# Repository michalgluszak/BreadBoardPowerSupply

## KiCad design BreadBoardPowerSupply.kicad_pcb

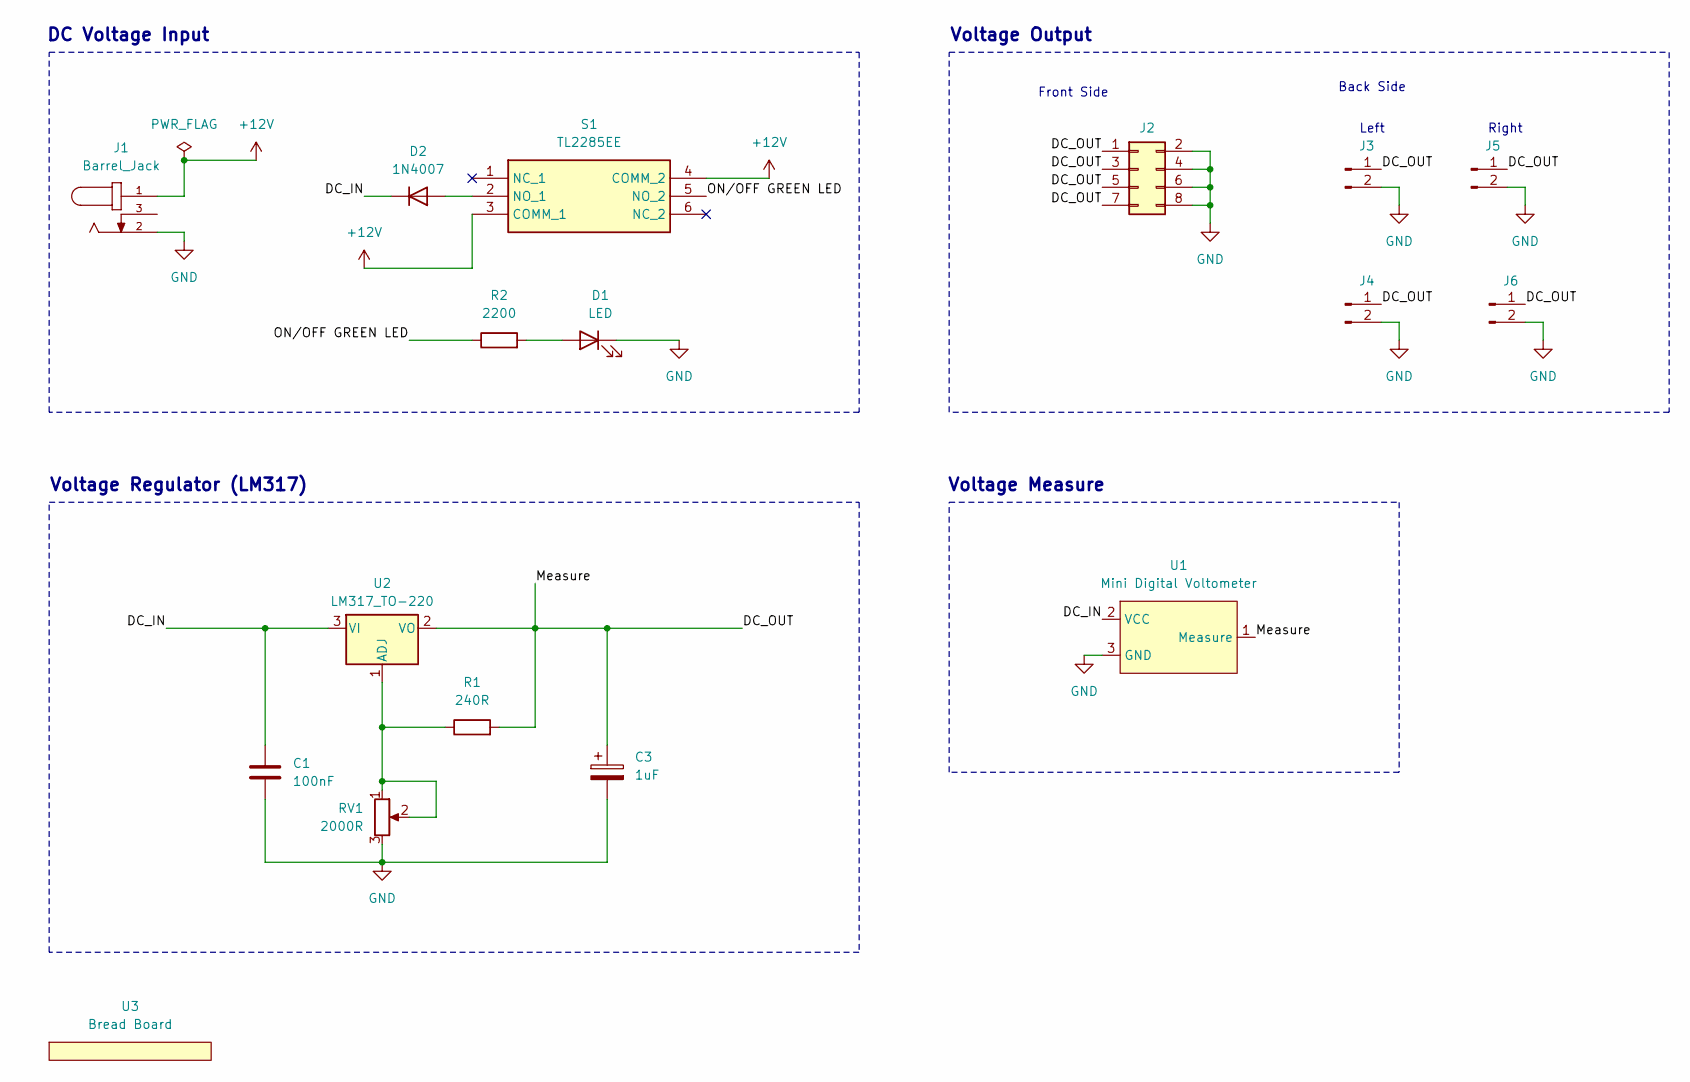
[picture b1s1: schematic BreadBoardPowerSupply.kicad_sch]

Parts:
C1: 100nF; C_0805_2012Metric_Pad1.18x1.45mm_HandSolder
C3: 1uF; C_0805_2012Metric_Pad1.18x1.45mm_HandSolder
D1: LED; LED_D3.0mm
D2: 1N4007; D_SMA_Handsoldering
J1: Barrel_Jack; GCT_DCJ200-10-A-XX-K_REVA; PARTREV A
J2: Conn_02x04_Odd_Even; PinHeader_2x04_P2.54mm_Vertical
J3, J4, J5, J6: Conn_01x02_Pin; PinHeader_1x02_P2.54mm_Vertical
R1: 240R; R_0805_2012Metric_Pad1.20x1.40mm_HandSolder
R2: 2200; R_0805_2012Metric_Pad1.20x1.40mm_HandSolder
RV1: 2000R; Potencjometr_WH148_3D
S1: TL2285EE; Manufacturer_Part_Number TL2285EE
U1: Mini Digital Voltometer; Mini_digital_voltmeter_with_hole
U2: LM317_TO-220; TO-220-3_Vertical
U3: Bread Board; Breadboard

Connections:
+12V: J1.1, S1.3 (COMM_1), S1.4 (COMM_2)
/DC_IN: C1.1, D2.1 (K), U1.2 (VCC), U2.3 (VI)
/DC_OUT: C3.1, J2.1, J2.3, J2.5, J2.7, J3.1, J4.1, J5.1, J6.1, R1.2, U1.1 (Measure), U2.2 (VO)
/ON/OFF GREEN LED: R2.1, S1.5 (NO_2)
GND: C1.2, C3.2, D1.1 (K), J1.2, J2.2, J2.4, J2.6, J2.8, J3.2, J4.2, J5.2, J6.2, RV1.3, U1.3 (GND)
unnamed: D1.2 (A), R2.2
unnamed: D2.2 (A), S1.2 (NO_1)
unnamed: R1.1, RV1.1, RV1.2, U2.1 (ADJ)

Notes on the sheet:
Left
Back Side
DC Voltage Input
Voltage Output
Right
Voltage Measure
Front Side
Voltage Regulator (LM317)

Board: 2 copper layers, 17 parts (4 on the bottom side), 8 nets, no tracks yet.

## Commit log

2026-06-28 Add .gitignore file
2026-06-28 All other files
2026-06-28 Add symbols
2026-06-28 Make electronic schematic
2026-06-28 Update electronics schematic
2026-06-28 Add footprints
2026-06-28 Another update
2026-06-28 Update schematic and add footprint for symbols
2026-06-28 Big update
